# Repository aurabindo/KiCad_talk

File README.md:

# Presentation on PCB design using KiCad

Made as a [reveal.js](https://github.com/hakimel/reveal.js) presentation - viewable at http://ianrrees.github.io/KiCad_talk/

All contents including example project are free to use under the [MIT license](https://opensource.org/licenses/MIT).

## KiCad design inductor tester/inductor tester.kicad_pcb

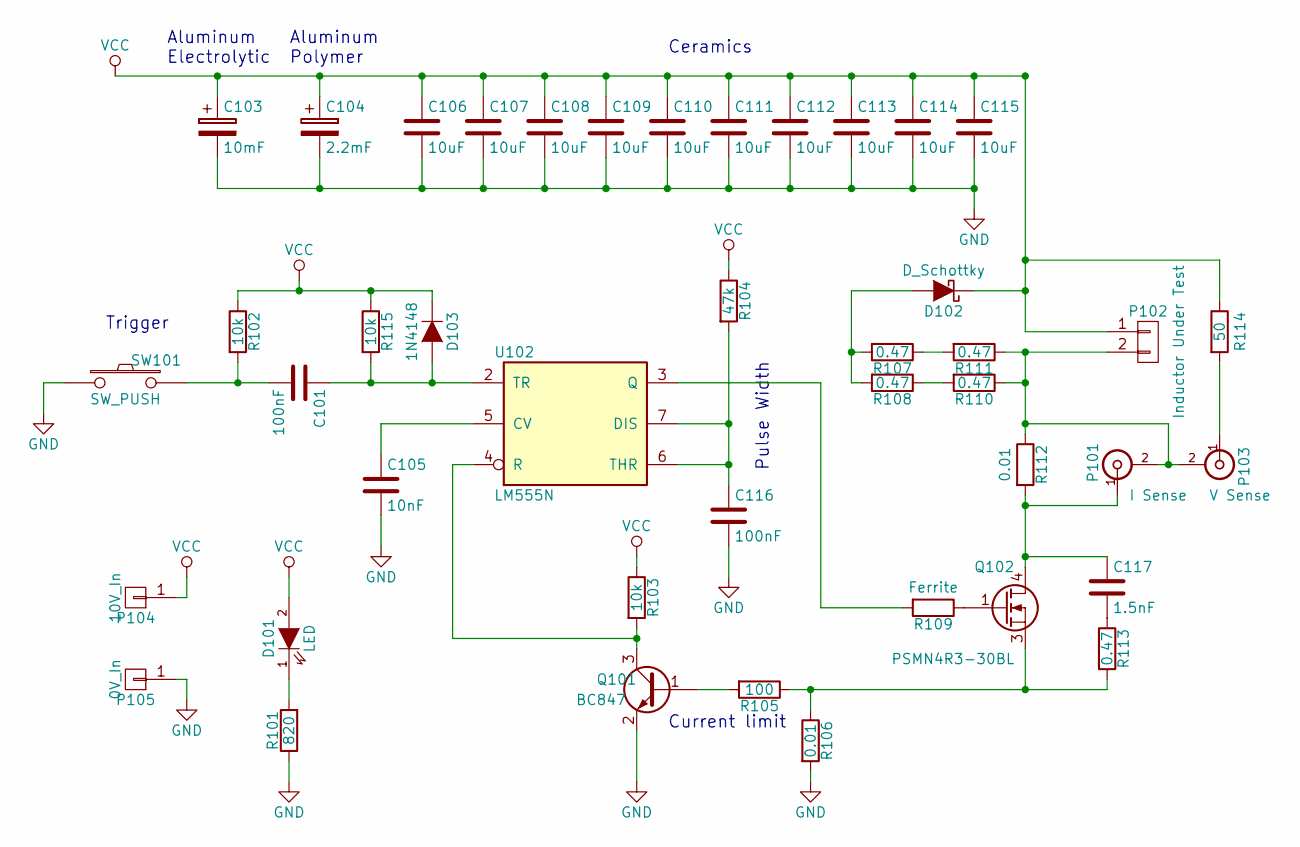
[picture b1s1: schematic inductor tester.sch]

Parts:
C101, C116: 100nF; C_0805_HandSoldering
C103: 10mF; C_Radial_D18_L36_P7.5
C104: 2.2mF; C_Radial_D10_L20_P5
C105: 10nF; C_0805_HandSoldering
C106, C107, C108, C109, C110, C111, C112, C113, C114, C115: 10uF; C_0805_HandSoldering
C117: 1.5nF; C_0805_HandSoldering
D101: LED; LED_0805
D102: D_Schottky; SOD-123
D103: 1N4148; MiniMELF_Standard
P101: I Sense; bnc-ci
P102: Inductor Under Test; AK300-2
P103: V Sense; bnc-ci
P104: 10V_In; Measurement_Point_Square-SMD-Pad_Big
P105: 0V_In; Measurement_Point_Square-SMD-Pad_Big
Q101: BC847; SOT-23_Handsoldering
Q102: PSMN4R3-30BL; TO-263-3Lead
R101: 820; R_0805_HandSoldering
R102, R103, R115: 10k; R_0805_HandSoldering
R104: 47k; R_0805_HandSoldering
R105: 100; R_0805_HandSoldering
R106, R112: 0.01; R_1206_HandSoldering
R107, R108, R110, R111: 0.47; R_1206_HandSoldering
R109: Ferrite; R_0805_HandSoldering
R113: 0.47; R_0805_HandSoldering
R114: 50; R_0805_HandSoldering
SW101: SW_PUSH; momentary_tactile_6x6x4
U102: LM555N; SOIJ-8_5.3x5.3mm_Pitch1.27mm

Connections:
GND: C103.2, C104.2, C105.2, C106.2, C107.2, C108.2, C109.2, C110.2, C111.2, C112.2, C113.2, C114.2, C115.2, C116.2, P105.1, Q101.2 (E), R101.1, R106.2, SW101.1, U102.1 (GND)
unnamed: C101.1, D103.2 (A), R115.2, U102.2 (TR)
unnamed: C101.2, R102.2, SW101.2
unnamed: C105.1, U102.5 (CV)
unnamed: C116.1, R104.2, U102.6 (THR), U102.7 (DIS)
unnamed: C117.1, P101.1 (In), Q102.4 (D), R112.2
unnamed: C117.2, R113.1
unnamed: D101.1 (K), R101.2
unnamed: D102.2 (A), R107.2, R108.2
unnamed: P101.2 (Ext), P102.2, P103.2 (Ext), R110.1, R111.1, R112.1
unnamed: P103.1 (In), R114.2
unnamed: Q101.1 (B), R105.2
unnamed: Q101.3 (C), R103.2, U102.4 (R)
unnamed: Q102.1 (G), R109.1
unnamed: Q102.3 (S), R105.1, R106.1, R113.2
unnamed: R107.1, R111.2
unnamed: R108.1, R110.2
unnamed: R109.2, U102.3 (Q)
VCC: C103.1, C104.1, C106.1, C107.1, C108.1, C109.1, C110.1, C111.1, C112.1, C113.1, C114.1, C115.1, D101.2 (A), D102.1 (K), D103.1 (K), P102.1, P104.1, R102.1, R103.1, R104.1, R114.1, R115.1, U102.8 (VCC)

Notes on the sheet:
Aluminum Electrolytic
Aluminum Polymer
Ceramics
Current limit
Trigger
Pulse Width

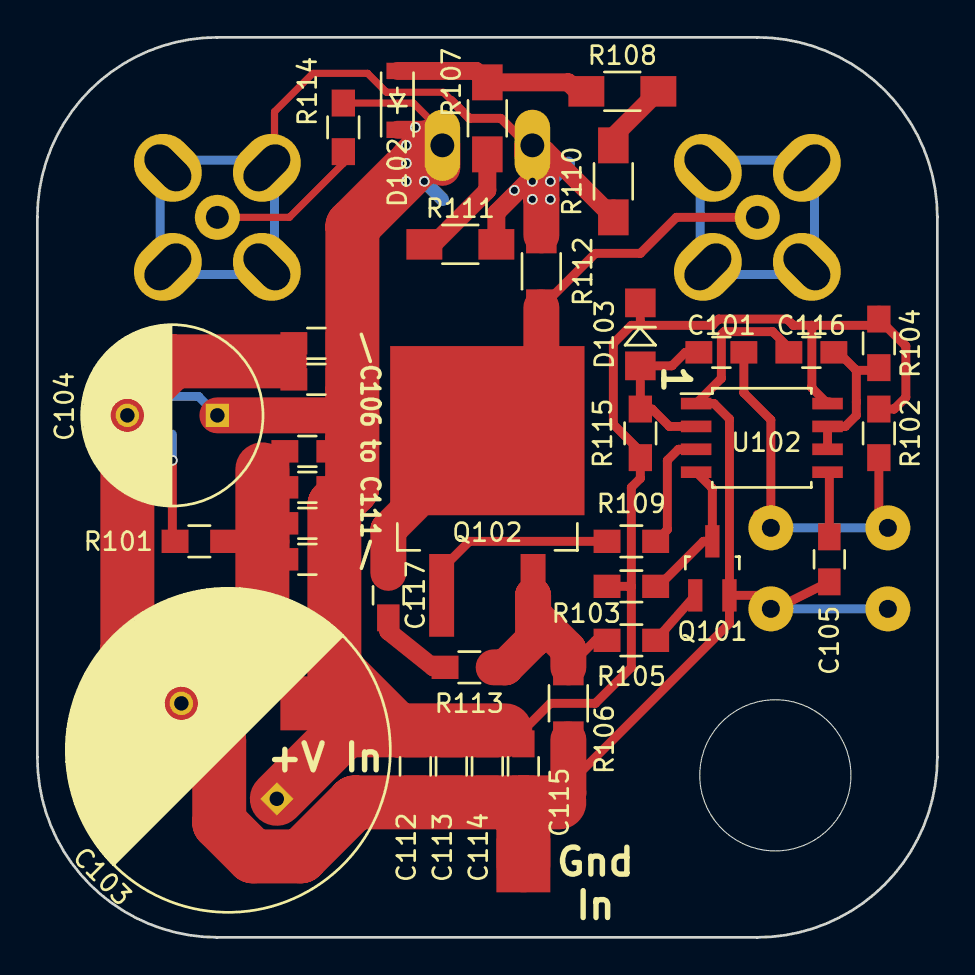
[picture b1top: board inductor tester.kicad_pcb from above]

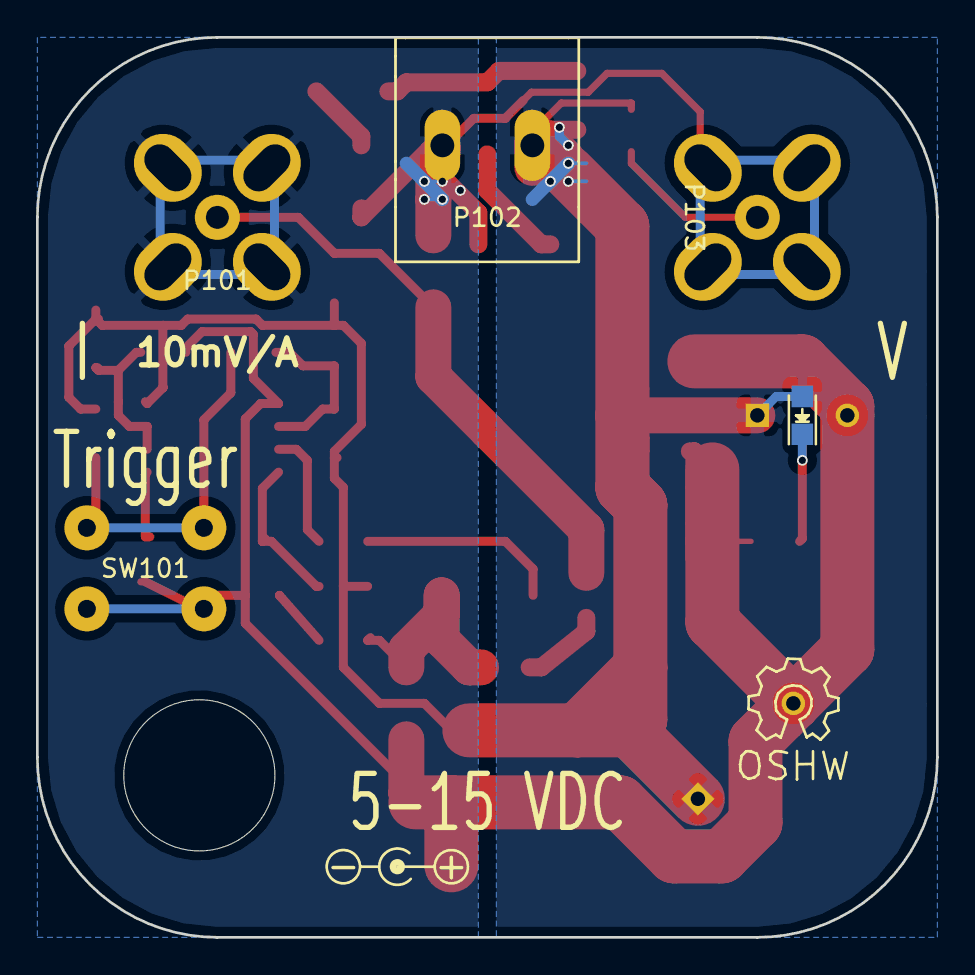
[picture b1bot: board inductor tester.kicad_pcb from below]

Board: 2 copper layers, 50.0 x 50.0 mm, 43 parts (5 on the bottom side), 19 nets.

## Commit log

2016-04-16 Just getting started on the KiCad parts
2016-04-16 Updated description/author
2016-04-18 Minor updates.
2016-04-25 Starting on layout
2016-04-26 Redid layout - presentation could use work.
2016-04-28 Bit of hacking on the presentation.
2016-04-28 Added spice sim demo
2016-04-28 Added notes on exporting, saved PCB as ordered.
2016-04-30 Updated talk - noticed pulse isn't fixed width...
2016-05-10 Fixed dumb spelling mistake.
2016-06-19 PCB v2 - several changes:
    * Fixed reset issue that caused current limit oscillation
    * Switched 555 to an easier-to-solder footprint
    * Better silkscreen labelling
    * Improved BNC footprints to accept wider variety of connectors
    * Thermal relief for through hole pads
    * Added OSHW logo
2016-06-22 Layout improvements, need to update BOM...
2017-09-25 Add slide on Kicad vs Eagle
2017-09-25 Remove Slide on example project
2017-09-25 Remove mention of example project from README.md
2017-09-25 Remove slide on Dirty PCB
